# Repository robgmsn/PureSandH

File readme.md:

View this project on [CADLAB.io](https://cadlab.io/project/24197). 

DESIGN STATUS: Awaiting Testing - Ready for beta testing

S&H Updated to V1.5 14/4/21

Library updated to include 3D models.
Traces rerouted.

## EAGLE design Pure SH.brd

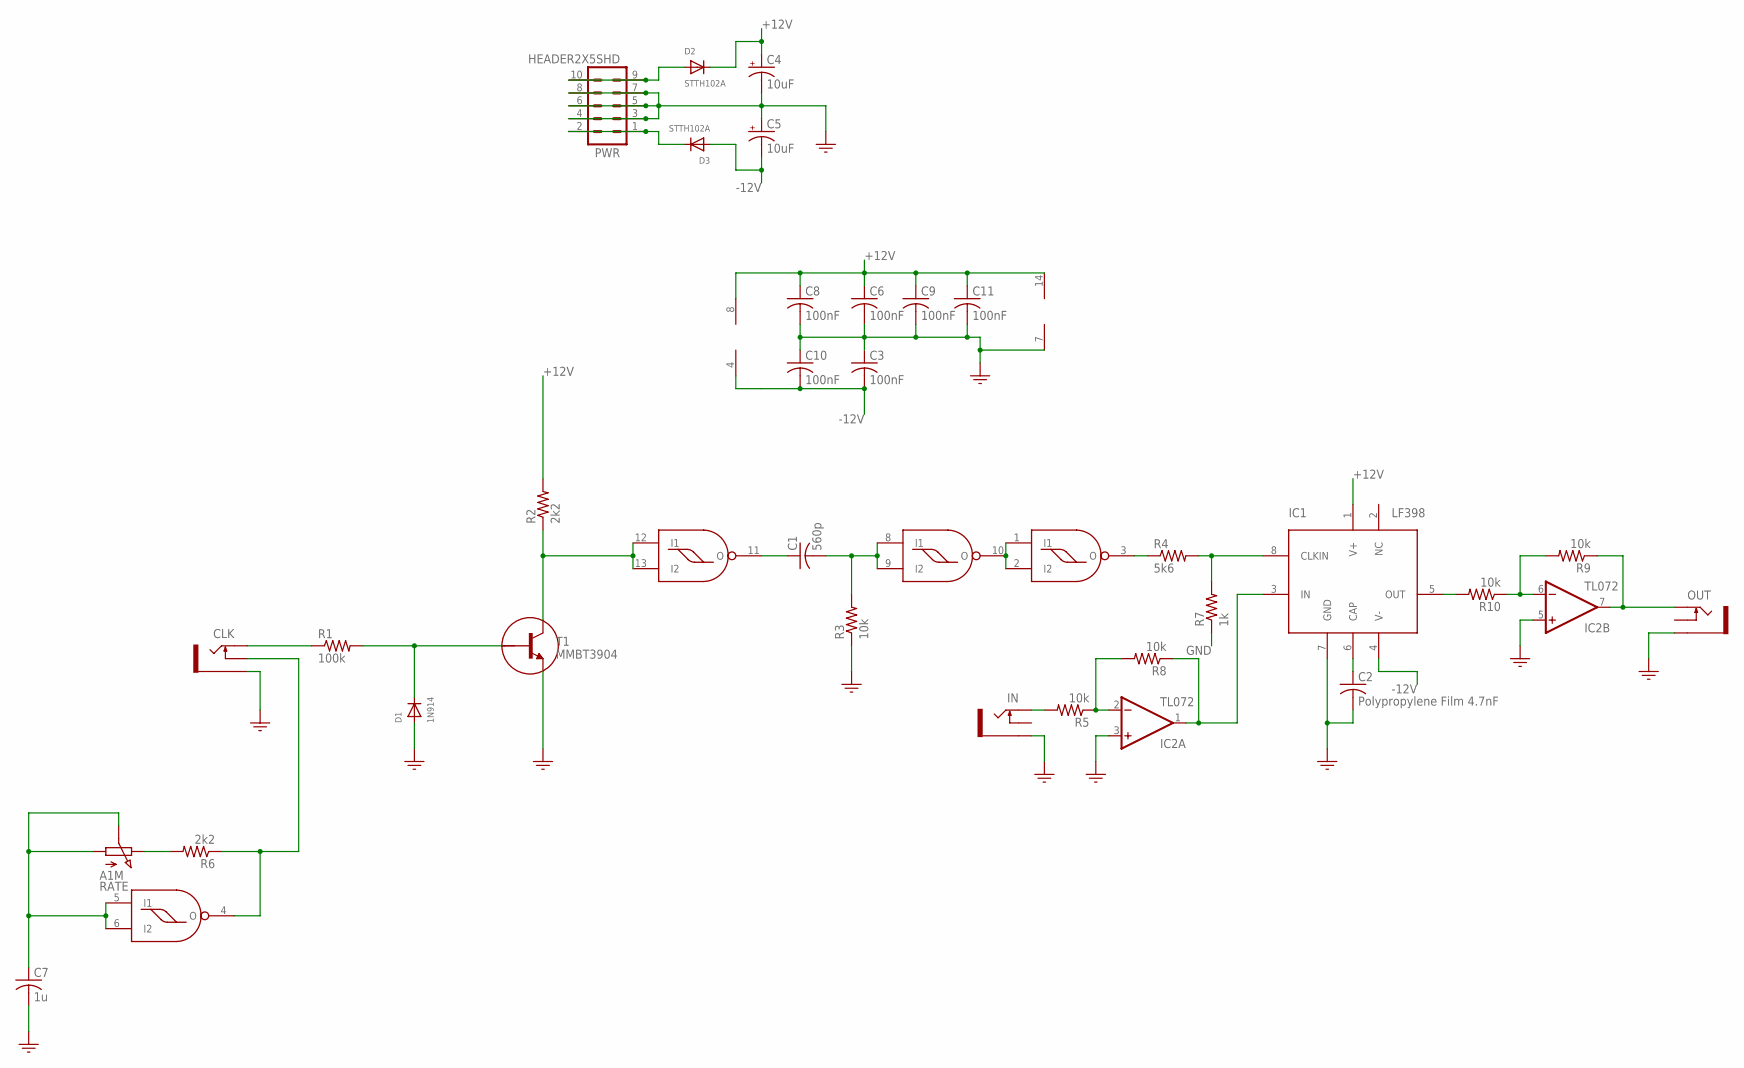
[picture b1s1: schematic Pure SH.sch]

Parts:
C1: 560p; C0805
C2: Polypropylene Film 4.7nF; C050-045X075
C3, C6, C8, C9, C10, C11: 100nF; C0805
C4, C5: 10uF; 153CLV-0505
C7: 1u; C0805
CLK: PJ301M-12
D1: 1N914; DO-41
D2, D3: STTH102A; SMADIODE
IC1: LF398; SOIC--8
IC2: TL072; SO08
IC3: cd4093; SOIC14
IN: PJ301M-12
OUT: PJ301M-12
PWR: HEADER2X5SHD; 2X5-SHROUDED
R1: 100k; R0805
R2, R6: 2k2; R0805
R3, R5, R8, R9, R10: 10k; R0805
R4: 5k6; R0805
R7: 1k; R0805
RATE: A1M; POTENTIOMETER_9MM
T1: MMBT3904; SOT23

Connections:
+12V: C4.+, C6.1, C8.1, C9.1, C11.1, D2.C, IC1.1 (V+), IC2.8 (V+), IC3.14 (V+), R2.2
-12V: C3.2, C5.-, C10.2, D3.A, IC1.4 (V-), IC2.4 (V-)
GND: C2.2, C3.1, C4.-, C5.+, C6.2, C7.2, C8.2, C9.2, C10.1, C11.2, CLK.GND (SLEEVE), D1.A, IC1.7 (GND), IC2.3 (+IN), IC2.5 (+IN), IC3.7 (V-), IN.GND (SLEEVE), OUT.GND (SLEEVE), PWR.3, PWR.4, PWR.5, PWR.6, PWR.7, PWR.8, R3.1, R7.1, T1.2 (E)
unnamed: CLK.TIP, R1.1
unnamed: D1.C, R1.2, T1.1 (B)
unnamed: C1.1, IC3.11 (O)
unnamed: IC3.12 (I1), IC3.13 (I2), R2.1, T1.3 (C)
unnamed: IC3.1 (I1), IC3.2 (I2), IC3.10 (O)
unnamed: IC1.8 (CLKIN), R4.2, R7.2
unnamed: C1.2, IC3.8 (I1), IC3.9 (I2), R3.2
unnamed: IC3.3 (O), R4.1
unnamed: C2.1, IC1.6 (CAP)
unnamed: IN.TIP, R5.2
unnamed: IC2.2 (-IN), R5.1, R8.2
unnamed: R6.2, RATE.P$3 (3)
unnamed: C7.1, IC3.5 (I1), IC3.6 (I2), RATE.P$1 (1), RATE.P$2 (2)
unnamed: CLK.NORM (SWITCH), IC3.4 (O), R6.1
unnamed: IC1.3 (IN), IC2.1 (OUT), R8.1
unnamed: IC1.5 (OUT), R10.2
unnamed: IC2.6 (-IN), R9.2, R10.1
unnamed: IC2.7 (OUT), OUT.TIP, R9.1
unnamed: D2.A, PWR.9, PWR.10
unnamed: D3.C, PWR.1, PWR.2

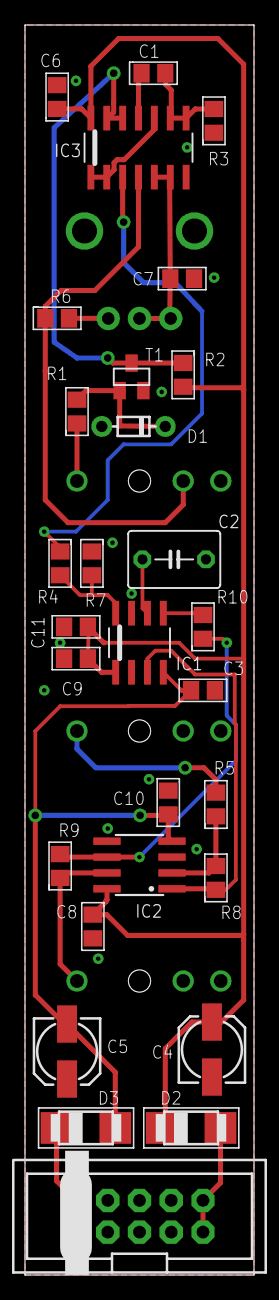
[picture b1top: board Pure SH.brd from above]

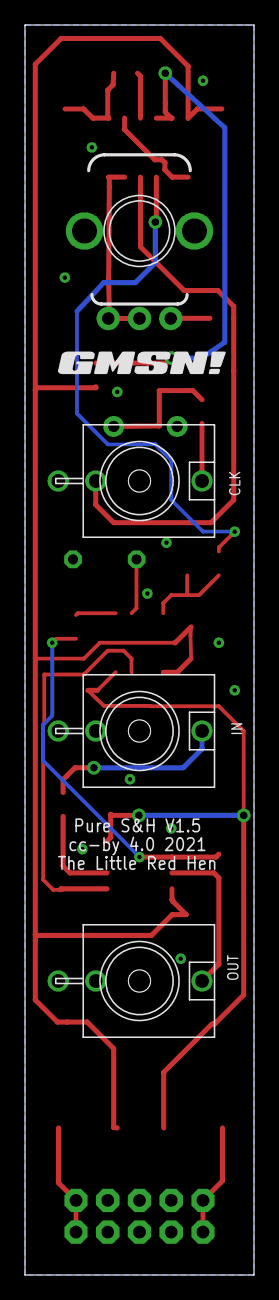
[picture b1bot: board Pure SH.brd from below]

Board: 2 copper layers, 18.3 x 100.0 mm, 34 parts (5 on the bottom side), 23 nets.

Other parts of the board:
U$3: GMSN!_LOGO

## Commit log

2021-04-16 SandH 1.1
2021-04-16 SandH 1.2
2021-04-16 SandH 1.3
2021-04-16 SandH 1.4
2021-04-16 SandH 1.5
    S&H Updated to V1.5 14/4/21
    Library updated to include 3D models.
    Traces rerouted.
2021-04-16 Backlink to CADLAB.io has been added.
2021-07-07 Reinstall

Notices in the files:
Pure SH.brd:
cc-by 4.0 2021
